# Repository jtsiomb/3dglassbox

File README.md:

3dglassbox - interface for 3D shutter glasses
=============================================
This is a versatile interface for driving 3D shutter glasses from a variety of
stereo sync sources.

Supported sync sources:
  - SGI 3-pin mini-DIN stereo port
  - SGI DE9 stereo port (IMPACT graphics)
  - VESA 3-pin mini-DIN stereo port
  - Frame-sequencial vsync toggle

Supported shutter glasses:
  - StereoGraphics CrystalEyes (IR)
  - ASUS VR100 (wired)

**Current status**: Under development. Not ready for use.

License
-------
Copyright (C) 2025 John Tsiombikas <nuclear@mutantstargoat.com>

You are free to use, reproduce, modify, and redistribute any part of this
project, provided you make any derivative work you release, freely available
under the same terms.

Both hardware designs, and software parts of this project, are released under
the terms of the GNU General Public License v3, or at your option any later
version published by the Free Software Foundation. See `LICENSE` for details.

To comply with the license, when releasing derivative hardware designs, you must
provide the full EDA project files, and of course firmware/software source code.
Releasing only images of schematics, gerbers, and firmware binaries is *not*
sufficient for compliance.

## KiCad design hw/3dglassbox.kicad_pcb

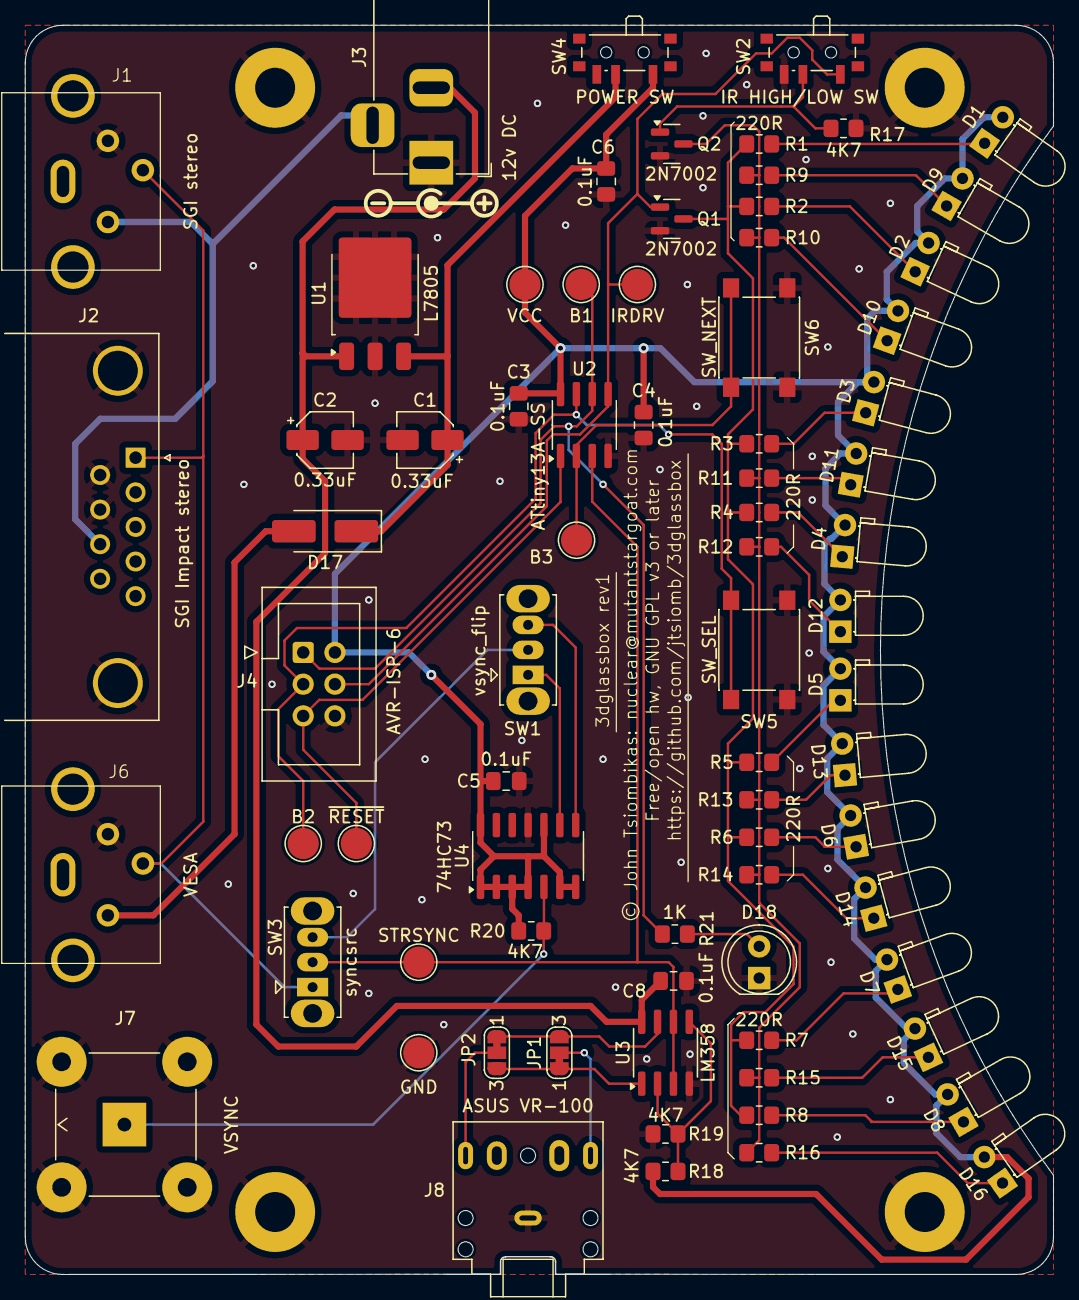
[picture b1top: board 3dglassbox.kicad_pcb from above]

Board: 2 copper layers, 82.2 x 99.9 mm, 78 parts (0 on the bottom side), 42 nets.

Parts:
B1, B2, B3: TestPoint; TestPoint_Pad_D2.5mm
C1, C2: 0.33uF; CP_Elec_4x5.4
C3, C4, C5, C6, C8: 0.1uF; C_0805_2012Metric_Pad1.18x1.45mm_HandSolder
D1, D2, D3, D4, D5, D6, D7, D8, D9, D10, D11, D12, D13, D14, D15, D16: IR LED; LED_D3.0mm_Horizontal_O1.27mm_Z2.0mm
D17: SS34; D_SMA_Handsoldering
D18: LED; LED_D5.0mm
GND: TestPoint; TestPoint_Pad_D2.5mm
H1, H2, H3, H4: MountingHole_Pad; MountingHole_3.2mm_M3_Pad
IRDRV: TestPoint; TestPoint_Pad_D2.5mm
J1: SGI stereo; minidin3
J2: SGI Impact stereo; DSUB-9_Male_Horizontal_P2.77x2.84mm_EdgePinOffset7.70mm_Hou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
J3: 12v DC; BarrelJack_Horizontal
J4: AVR-ISP-6; IDC-Header_2x03_P2.54mm_Vertical
J6: VESA; minidin3
J7: VSYNC; BNC_TEConnectivity_1478035_Horizontal
J8: ASUS VR-100; Jack_3.5mm_CUI_SJ1-3525N_Horizontal
JP1: JPOL1; SolderJumper-3_P1.3mm_Bridged12_RoundedPad1.0x1.5mm_NumberL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
JP2: JPOL2; SolderJumper-3_P1.3mm_Bridged12_RoundedPad1.0x1.5mm_NumberL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
Q1, Q2: 2N7002; SOT-23
R1, R2, R3, R4, R5, R6, R7, R8, R9, R10, R11, R12, R13, R14, R15, R16: 220R; R_0805_2012Metric_Pad1.20x1.40mm_HandSolder
R17, R18, R19, R20: 4K7; R_0805_2012Metric_Pad1.20x1.40mm_HandSolder
R21: 1K; R_0805_2012Metric_Pad1.20x1.40mm_HandSolder
STRSYNC: TestPoint; TestPoint_Pad_D2.5mm
SW1: vsync_flip; SW_Slide_SPDT_Straight_CK_OS102011MS2Q
SW2: IR HIGH/LOW SW; SW_SPDT_PCM12
SW3: syncsrc; SW_Slide_SPDT_Straight_CK_OS102011MS2Q
SW4: POWER SW; SW_SPDT_PCM12
SW5: SW_SEL; SW_Push_1P1T_NO_6x6mm_H9.5mm
SW6: SW_NEXT; SW_Push_1P1T_NO_6x6mm_H9.5mm
U1: L7805; TO-252-3_TabPin2
U2: ATtiny13A-SS; SOIC-8_3.9x4.9mm_P1.27mm
U3: LM358; SOIC-8_3.9x4.9mm_P1.27mm
U4: 74HC73; SO-14_3.9x8.65mm_P1.27mm
VCC: TestPoint; TestPoint_Pad_D2.5mm

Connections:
+5V: C1.1, D17.1 (K), SW4.2 (B), U1.3 (OUT)
+12V: C2.1, C8.1, J3.2, U1.1 (IN), U3.8 (V+)
/B1: B1.1, J4.1 (MISO), R21.1, U2.6 (PB1)
/B2: B2.1, J4.3 (SCK), SW5.1, U2.7 (PB2)
/B3: B3.1, SW6.1, U2.2 (PB3)
/IRDRV: IRDRV.1, J4.4 (MOSI), Q1.1 (G), SW2.1 (A), U2.5 (PB0)
/STEREOIN: J1.3, J2.1, J6.3, SW3.1 (A)
/STRSYNC: STRSYNC.1, SW3.2 (B), U2.3 (PB4), U3.3 (+), U3.6 (-)
/VSYNC: J7.1 (In), R20.2, U4.5 (C)
/~RESET: J4.5 (~RST), U2.1 (~RESET/PB5)
GND: C1.2, C2.2, C3.2, C4.2, C5.2, C6.2, C8.2, D18.1 (K), GND.1, H1.1, H2.1, H3.1, H4.1, J1.2, J2.0 (PAD), J2.6, J2.7, J3.1, J4.6 (GND), J6.2, J7.2 (Ext), J8.S, Q1.2 (S), Q2.2 (S), R17.1, R19.2, SW2.3 (C), SW5.2, SW6.2, U1.2 (GND), U2.4 (GND), U3.4 (V-), U4.11 (GND)
unnamed: D1.1 (K), R1.1
unnamed: D2.1 (K), R2.1
unnamed: D3.1 (K), R3.1
unnamed: D4.1 (K), R4.1
unnamed: D5.1 (K), R5.1
unnamed: D6.1 (K), R6.1
unnamed: D7.1 (K), R7.1
unnamed: D8.1 (K), R8.1
unnamed: D9.1 (K), R9.1
unnamed: D10.1 (K), R10.1
unnamed: D11.1 (K), R11.1
unnamed: D12.1 (K), R12.1
unnamed: D13.1 (K), R13.1
unnamed: D14.1 (K), R14.1
unnamed: D15.1 (K), R15.1
unnamed: D16.1 (K), R16.1
unnamed: D17.2 (A), J6.1
unnamed: D18.2 (A), R21.2
unnamed: JP1.1 (A), JP2.3 (B), U3.1
unnamed: JP1.3 (B), JP2.1 (A), U3.7
unnamed: J8.T, JP1.2 (C)
unnamed: J8.R, JP2.2 (C)
unnamed: Q1.3 (D), R1.2, R2.2, R3.2, R4.2, R5.2, R6.2, R7.2, R8.2
unnamed: Q2.3 (D), R9.2, R10.2, R11.2, R12.2, R13.2, R14.2, R15.2, R16.2
unnamed: Q2.1 (G), R17.2, SW2.2 (B)
unnamed: SW1.1 (A), U4.9 (Q)
unnamed: SW1.2 (B), SW3.3 (C)
unnamed: SW1.3 (C), U4.8 (~Q)
unnamed: R18.2, R19.1, U3.2 (-), U3.5 (+)
VBUS: J1.1, J2.8, J3.3
VCC: C3.1, C4.1, C5.1, C6.1, D1.2 (A), D2.2 (A), D3.2 (A), D4.2 (A), D5.2 (A), D6.2 (A), D7.2 (A), D8.2 (A), D9.2 (A), D10.2 (A), D11.2 (A), D12.2 (A), D13.2 (A), D14.2 (A), D15.2 (A), D16.2 (A), J4.2 (VCC), R18.1, R20.1, SW4.1 (A), U2.8 (VCC), U4.1 (C), U4.2 (~R), U4.3 (K), U4.4 (VCC), U4.6 (~R), U4.7 (J), U4.10 (K), U4.14 (J), VCC.1

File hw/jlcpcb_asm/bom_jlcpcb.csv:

Comment,Designator,Footprint,LCSC
"0.33uF","C1,C2","Capacitor_SMD:CP_Elec_4x5.4","C264238"
"0.1uF","C3,C4,C5,C6,C8","Capacitor_SMD:C_0805_2012Metric_Pad1.18x1.45mm_HandSolder","C49678"
"IR LED","D1,D2,D3,D4,D5,D6,D7,D8,D9,D10,D11,D12,D13,D14,D15,D16","LED_THT:LED_D3.0mm_Horizontal_O1.27mm_Z2.0mm",""
"SS34","D17","Diode_SMD:D_SMA_Handsoldering",""
"LED","D18","LED_THT:LED_D5.0mm","C2895492"
"SGI stereo","J1","3dglassbox:minidin3","C20611697"
"SGI Impact stereo","J2","Connector_Dsub:DSUB-9_Male_Horizontal_P2.77x2.84mm_EdgePinOffset7.70mm_Housed_MountingHolesOffset9.12mm","C7498157"
"12v DC","J3","Connector_BarrelJack:BarrelJack_Horizontal","C962225"
"AVR-ISP-6","J4","Connector_IDC:IDC-Header_2x03_P2.54mm_Vertical","C4749192"
"VESA","J6","3dglassbox:minidin3","C20611697"
"VSYNC","J7","Connector_Coaxial:BNC_TEConnectivity_1478035_Horizontal","C521209"
"ASUS VR-100","J8","Connector_Audio:Jack_3.5mm_CUI_SJ1-3525N_Horizontal","C692542"
"2N7002","Q1,Q2","Package_TO_SOT_SMD:SOT-23","C8545"
"220R","R1,R2,R3,R4,R5,R6,R7,R8,R9,R10,R11,R12,R13,R14,R15,R16","Resistor_SMD:R_0805_2012Metric_Pad1.20x1.40mm_HandSolder","C17557"
"4K7","R17,R18,R19,R20","Resistor_SMD:R_0805_2012Metric_Pad1.20x1.40mm_HandSolder","C17673"
"1K","R21","Resistor_SMD:R_0805_2012Metric_Pad1.20x1.40mm_HandSolder","C17513"
"vsync_flip","SW1","Button_Switch_THT:SW_Slide_SPDT_Straight_CK_OS102011MS2Q","C136719"
"IR HIGH/LOW SW","SW2","Button_Switch_SMD:SW_SPDT_PCM12","C431541"
"syncsrc","SW3","Button_Switch_THT:SW_Slide_SPDT_Straight_CK_OS102011MS2Q","C136719"
"POWER SW","SW4","Button_Switch_SMD:SW_SPDT_PCM12","C431541"
"SW_SEL","SW5","Button_Switch_SMD:SW_Push_1P1T_NO_6x6mm_H9.5mm","C455110"
"SW_NEXT","SW6","Button_Switch_SMD:SW_Push_1P1T_NO_6x6mm_H9.5mm","C455110"
"L7805","U1","Package_TO_SOT_SMD:TO-252-3_TabPin2","C21706"
"ATtiny13A-SS","U2","Package_SO:SOIC-8_3.9x4.9mm_P1.27mm","C40382"
"LM358","U3","Package_SO:SOIC-8_3.9x4.9mm_P1.27mm","C7950"
"74HC73","U4","Package_SO:SO-14_3.9x8.65mm_P1.27mm","C350539"

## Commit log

2025-03-29 pcb design done
2025-03-29 change portb config to match current schematic (buttons)
2025-03-29 front PCB cutout, to avoid blocking the IR LEDs from below
2025-03-29 added jlcpcb assembly files
2025-03-29 let's just commit the gerbers too
2025-04-28 make it clear in the readme, that this isn't done yet

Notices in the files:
hw/3dglassbox.kicad_pcb:
© John Tsiombikas: nuclear@mutantstargoat.com
Free/open hw, GNU GPL v3 or later
